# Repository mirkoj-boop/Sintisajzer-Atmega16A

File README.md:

# 🎹 Razvoj jednostavnog digitalno upravljanog sintisajzera temeljenog na mikroupravljaču ATmega16A

**** jednostavni PCB dizajn:
- **ATMEGA16-A** kao digitalni Oscilator
- an **LM386 preamplifier** pretpojačalo za 8 Ω zvučnik.

Dizajnirano jednostavno pojačalo za sintisajzer

1. Inicijaliziraj I2C komunikaciju
2. Inicijaliziraj tri MCP23008 čipa (postavi sve pinove kao ulaze)
3. Beskonačno ponavljaj:
   a. Pročitaj stanje tipki s prva tri MCP23008 čipa (8 tipki po čipu, ukupno 24)
   b. Inverzija očitanja (jer su tipke aktivne na LOW)
   c. Provjeri pritisnute tipke u sljedećem redoslijedu:
      - Za prvi čip (tipke 0-7):
        Ako je neka tipka pritisnuta, pošalji vrijednost note (notes[0-7]) na DAC i prekini
      - Ako nema pritisnutih tipki na prvom čipu, provjeri drugi čip (tipke 8-15):
        Ako je neka tipka pritisnuta26, pošalji vrijednost note (notes[8-15]) na DAC i prekini
      - Ako nema pritisnutih tipki na drugom čipu, provjeri treći čip (tipke 16-23):
        Ako je neka tipka pritisnuta, pošalji vrijednost note (notes[16-23]) na DAC i prekini
      - Ako nijedna tipka nije pritisnuta, postavi DAC na 0 (tišina)
   d. Pričekaj 10 ms prije sljedećeg očitavanja

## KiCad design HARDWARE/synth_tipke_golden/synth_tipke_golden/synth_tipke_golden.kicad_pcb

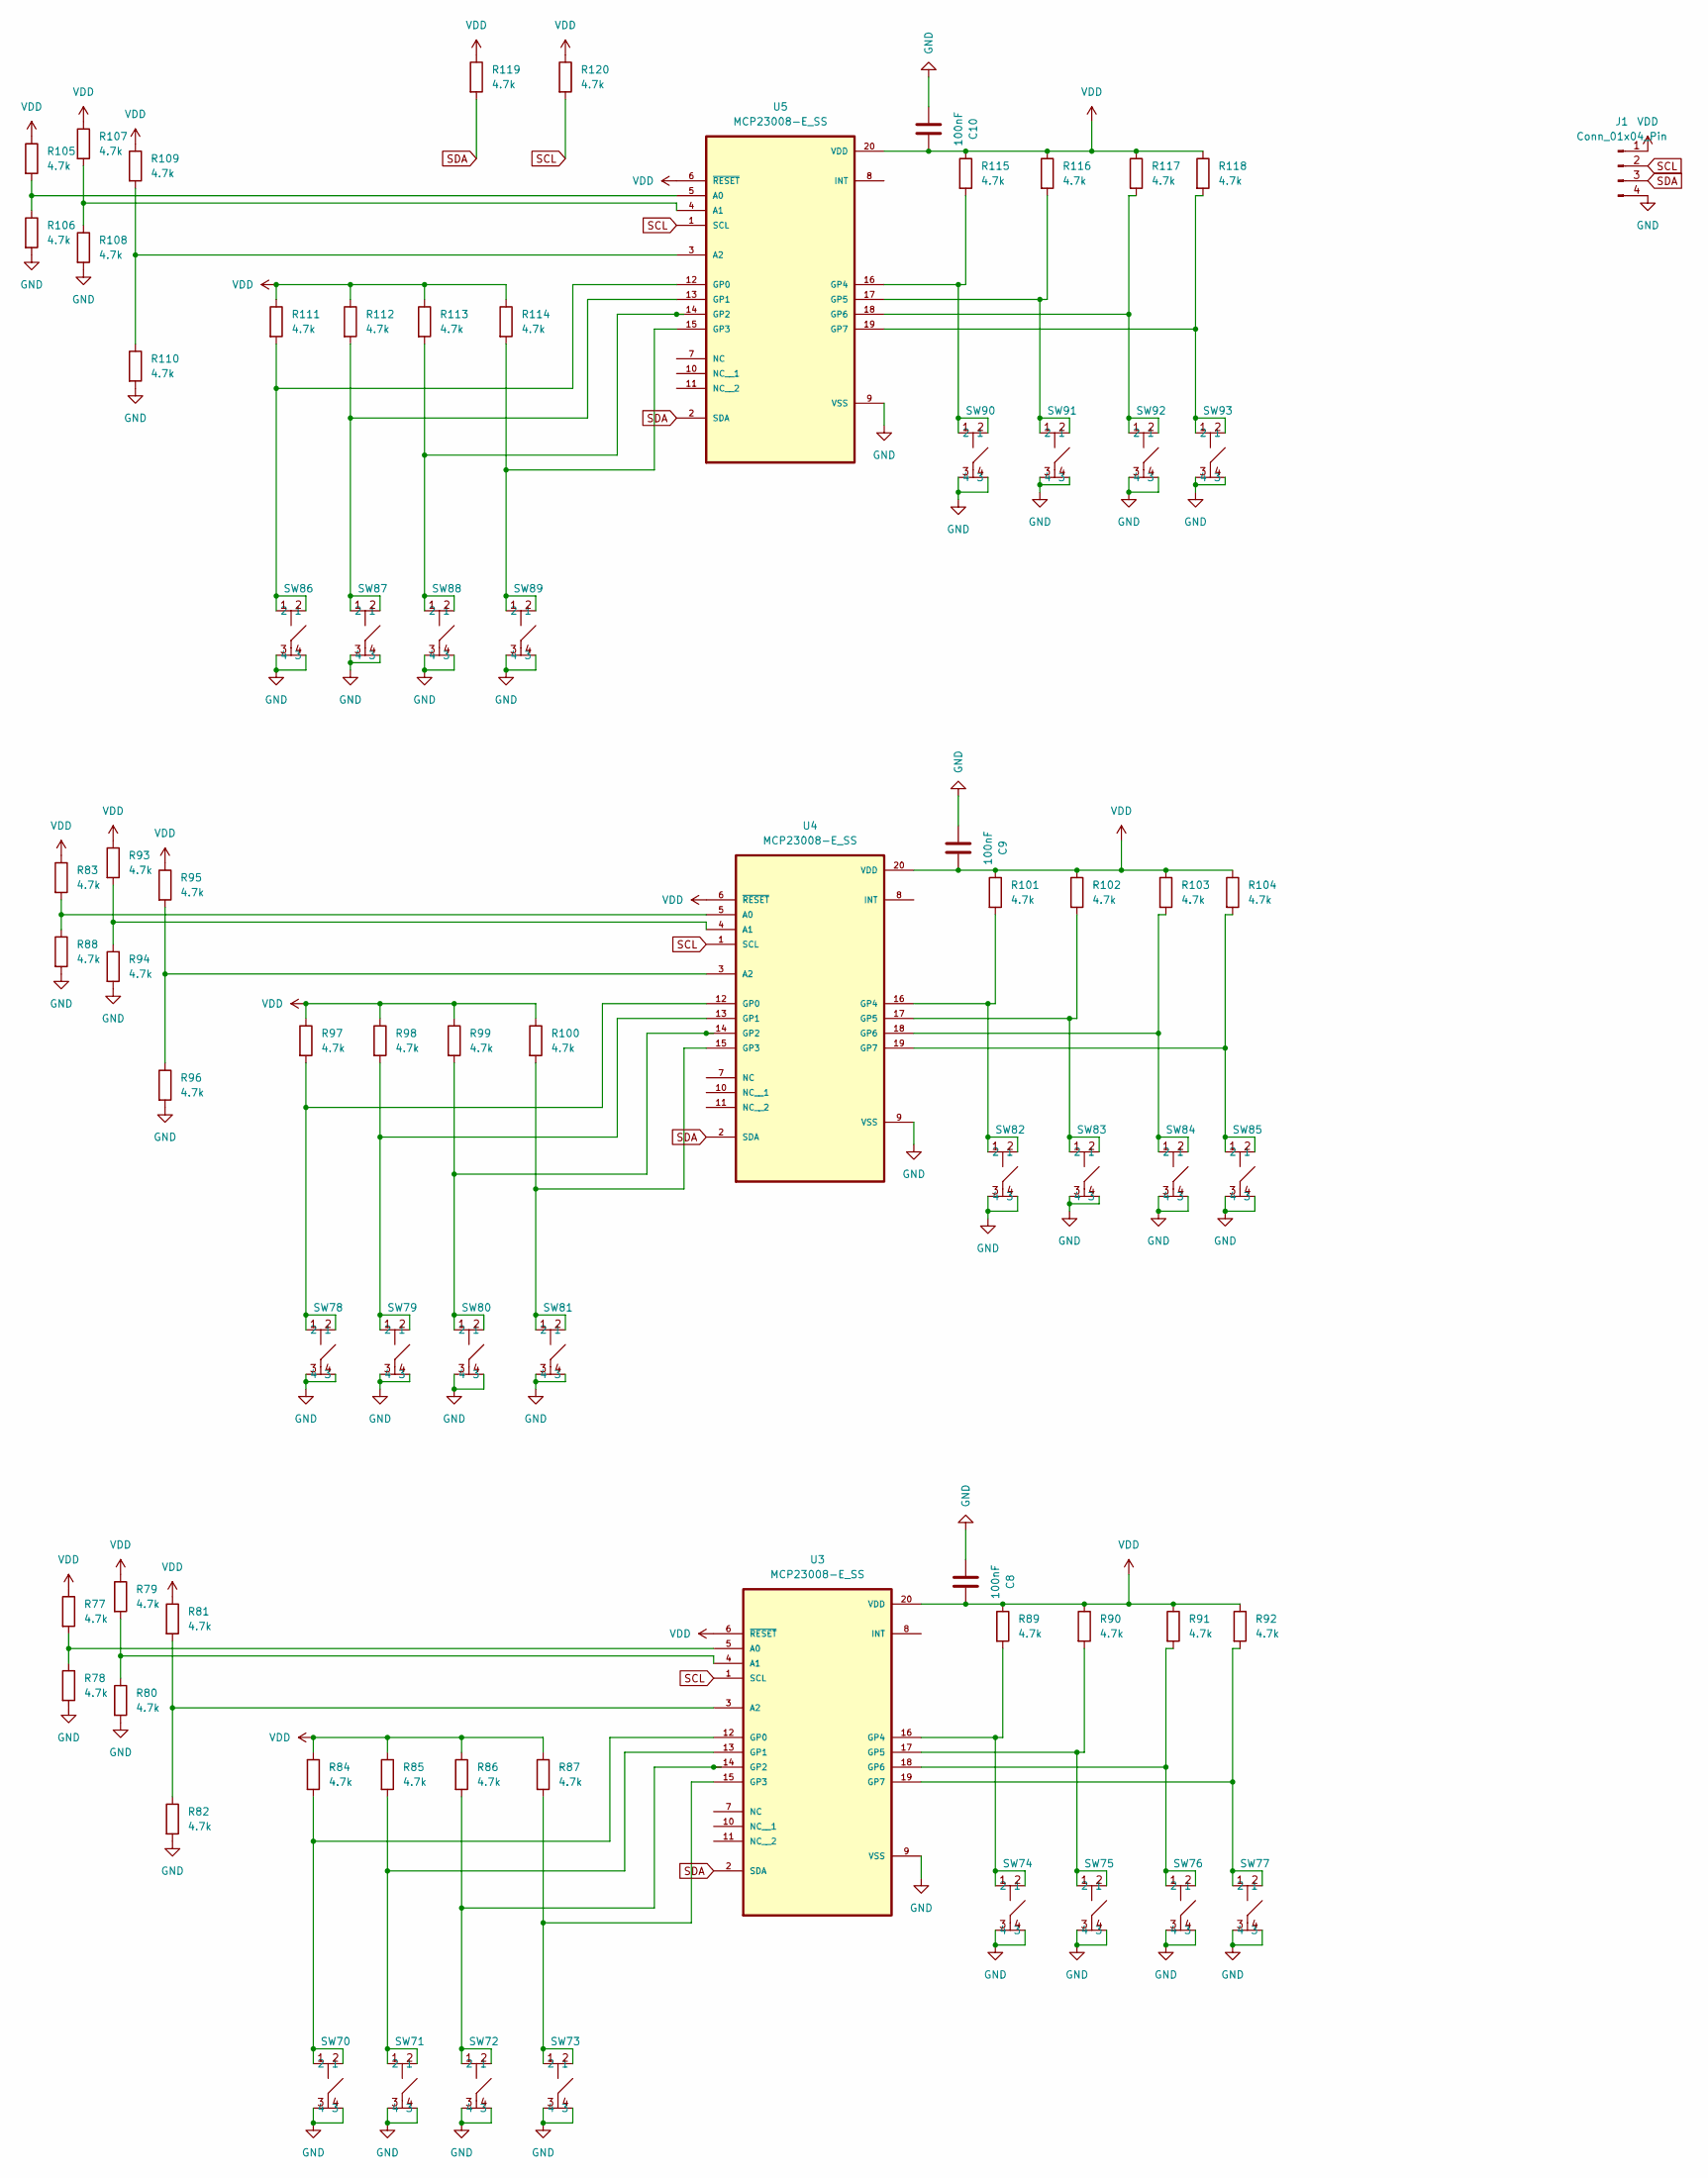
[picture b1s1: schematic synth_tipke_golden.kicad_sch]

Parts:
C8, C9, C10: 100nF; C_0201_0603Metric
J1: Conn_01x04_Pin; JST_EH_B4B-EH-A_1x04_P2.50mm_Vertical
R77, R78, R79, R80, R81, R82, R83, R84, R85, R86, R87, R88, R89, R90, R91, R92, R93, R94, R95, R96, R97, R98, R99, R100, R101, R102, R103, R104, R105, R106, R107, R108, R109, R110, R111, R112, R113, R114, R115, R116, R117, R118, R119, R120: 4.7k; R_0201_0603Metric
SW70, SW71, SW72, SW73, SW74, SW75, SW76, SW77, SW78, SW79, SW80, SW81, SW82, SW83, SW84, SW85, SW86, SW87, SW88, SW89, SW90, SW91, SW92, SW93: PTS530
U3, U4, U5: MCP23008-E_SS; SOP65P780X200-20N

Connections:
GND: C8.1, C9.1, C10.1, J1.4, R78.2, R80.2, R82.2, R88.2, R94.2, R96.2, R106.2, R108.2, R110.2, SW70.3, SW70.4, SW71.3, SW71.4, SW72.3, SW72.4, SW73.3, SW73.4, SW74.3, SW74.4, SW75.3, SW75.4, SW76.3, SW76.4, SW77.3, SW77.4, SW78.3, SW78.4, SW79.3, SW79.4, SW80.3, SW80.4, SW81.3, SW81.4, SW82.3, SW82.4, SW83.3, SW83.4, SW84.3, SW84.4, SW85.3, SW85.4, SW86.3, SW86.4, SW87.3, SW87.4, SW88.3, SW88.4, SW89.3, SW89.4, SW90.3, SW90.4, SW91.3, SW91.4, SW92.3, SW92.4, SW93.3, SW93.4, U3.9 (VSS), U4.9 (VSS), U5.9 (VSS)
unnamed: R77.2, R78.1, U3.5 (A0)
unnamed: R79.2, R80.1, U3.4 (A1)
unnamed: R81.2, R82.1, U3.3 (A2)
unnamed: R84.2, SW70.1, SW70.2, U3.12 (GP0)
unnamed: R85.2, SW71.1, SW71.2, U3.13 (GP1)
unnamed: R86.2, SW72.1, SW72.2, U3.14 (GP2)
unnamed: R87.2, SW73.1, SW73.2, U3.15 (GP3)
unnamed: R89.2, SW74.1, SW74.2, U3.16 (GP4)
unnamed: R90.2, SW75.1, SW75.2, U3.17 (GP5)
unnamed: R91.2, SW76.1, SW76.2, U3.18 (GP6)
unnamed: R92.2, SW77.1, SW77.2, U3.19 (GP7)
unnamed: R83.2, R88.1, U4.5 (A0)
unnamed: R93.2, R94.1, U4.4 (A1)
unnamed: R95.2, R96.1, U4.3 (A2)
unnamed: R97.2, SW78.1, SW78.2, U4.12 (GP0)
unnamed: R98.2, SW79.1, SW79.2, U4.13 (GP1)
unnamed: R99.2, SW80.1, SW80.2, U4.14 (GP2)
unnamed: R100.2, SW81.1, SW81.2, U4.15 (GP3)
unnamed: R101.2, SW82.1, SW82.2, U4.16 (GP4)
unnamed: R102.2, SW83.1, SW83.2, U4.17 (GP5)
unnamed: R103.2, SW84.1, SW84.2, U4.18 (GP6)
unnamed: R104.2, SW85.1, SW85.2, U4.19 (GP7)
unnamed: R105.2, R106.1, U5.5 (A0)
unnamed: R107.2, R108.1, U5.4 (A1)
unnamed: R109.2, R110.1, U5.3 (A2)
unnamed: R111.2, SW86.1, SW86.2, U5.12 (GP0)
unnamed: R112.2, SW87.1, SW87.2, U5.13 (GP1)
unnamed: R113.2, SW88.1, SW88.2, U5.14 (GP2)
unnamed: R114.2, SW89.1, SW89.2, U5.15 (GP3)
unnamed: R115.2, SW90.1, SW90.2, U5.16 (GP4)
unnamed: R116.2, SW91.1, SW91.2, U5.17 (GP5)
unnamed: R117.2, SW92.1, SW92.2, U5.18 (GP6)
unnamed: R118.2, SW93.1, SW93.2, U5.19 (GP7)
SCL: J1.2, R120.2, U3.1 (SCL), U4.1 (SCL), U5.1 (SCL)
SDA: J1.3, R119.2, U3.2 (SDA), U4.2 (SDA), U5.2 (SDA)
VDD: C8.2, C9.2, C10.2, J1.1, R77.1, R79.1, R81.1, R83.1, R84.1, R85.1, R86.1, R87.1, R89.1, R90.1, R91.1, R92.1, R93.1, R95.1, R97.1, R98.1, R99.1, R100.1, R101.1, R102.1, R103.1, R104.1, R105.1, R107.1, R109.1, R111.1, R112.1, R113.1, R114.1, R115.1, R116.1, R117.1, R118.1, R119.1, R120.1, U3.6 (~RESET), U3.20 (VDD), U4.6 (~RESET), U4.20 (VDD), U5.6 (~RESET), U5.20 (VDD)

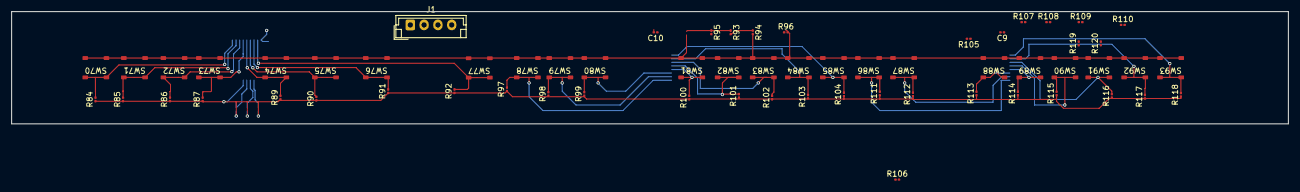
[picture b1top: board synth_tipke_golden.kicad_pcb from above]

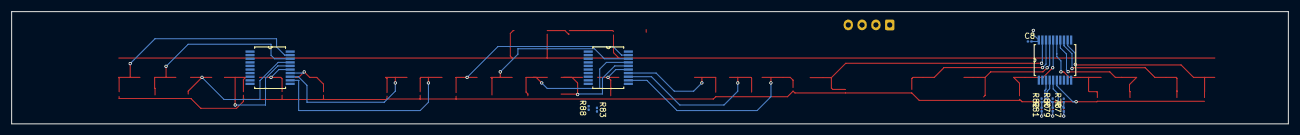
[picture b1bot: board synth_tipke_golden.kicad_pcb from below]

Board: 2 copper layers, 231.1 x 20.3 mm, 75 parts (12 on the bottom side), 37 nets.

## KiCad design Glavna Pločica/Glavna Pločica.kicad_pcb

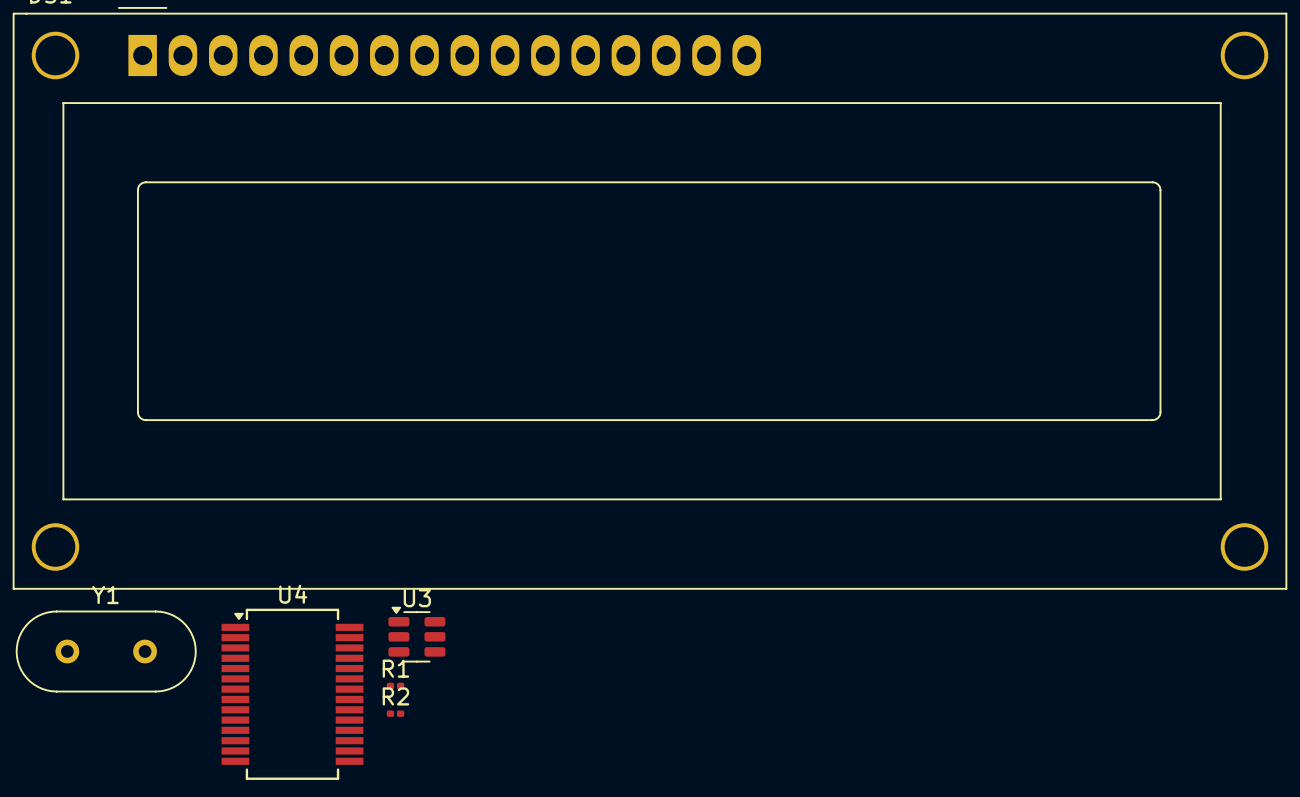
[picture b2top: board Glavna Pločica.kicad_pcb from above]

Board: 2 copper layers, 6 parts (0 on the bottom side), 4 nets, no tracks yet.

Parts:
DS1: WC1602A
R1, R2: 4.7k; R_0201_0603Metric
U3: MCP4725xxx-xCH; SOT-23-6
U4: FT232RL; SSOP-28_5.3x10.2mm_P0.65mm
Y1: Crystal; Crystal_HC18-U_Vertical

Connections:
GND: DS1.1 (VSS), DS1.16 (LED(-)), U3.2 (VSS)
unnamed: R2.1, U3.5 (SCL)
unnamed: R1.1, U3.4 (SDA)
VCC: DS1.2 (VDD), DS1.3 (VO), DS1.15 (LED(+)), U3.3 (VDD), U3.6 (A0)

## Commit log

2025-07-12 Update README.md
    Changed description
2025-07-12 FIrst push
    Project initialized
2025-07-12 Second push from laptop work
    Removed RC filter
2025-07-17 Kod potreban za pokretanje zvuka sa pločice
2025-07-18 Promijena lm386 da moze G = 200
    Ubačena trikondenzatora, jedan na ulaz pin 6 za čišće leveliranje zvuka, jedan između 1 i 8 kako bi dobili pojačanje 200 i jedan RC filter vraćen prije zvučnika
2025-07-18 Ispravka tipki
2025-07-24 I2C inicijalizacija
2025-07-25 sitne ispravke
2025-07-25 Ispravke Koda
    Ispravak koda na smjerovima Input/output registra
2025-07-27 Testiranje testiranja
2025-08-01 Velike promjene
    Promjene afektirane sa avr library https://avrdudes.github.io/avr-libc/
2025-08-04 Ipsravka jako puno stvari
2025-08-12 Dodan Sawtooth i lcd
    Dodani su timeri, asm nop za zastoj, dodan je lcd na portu a i izbacen usart kao testiranje
2025-08-29 Fixing names and call backs
